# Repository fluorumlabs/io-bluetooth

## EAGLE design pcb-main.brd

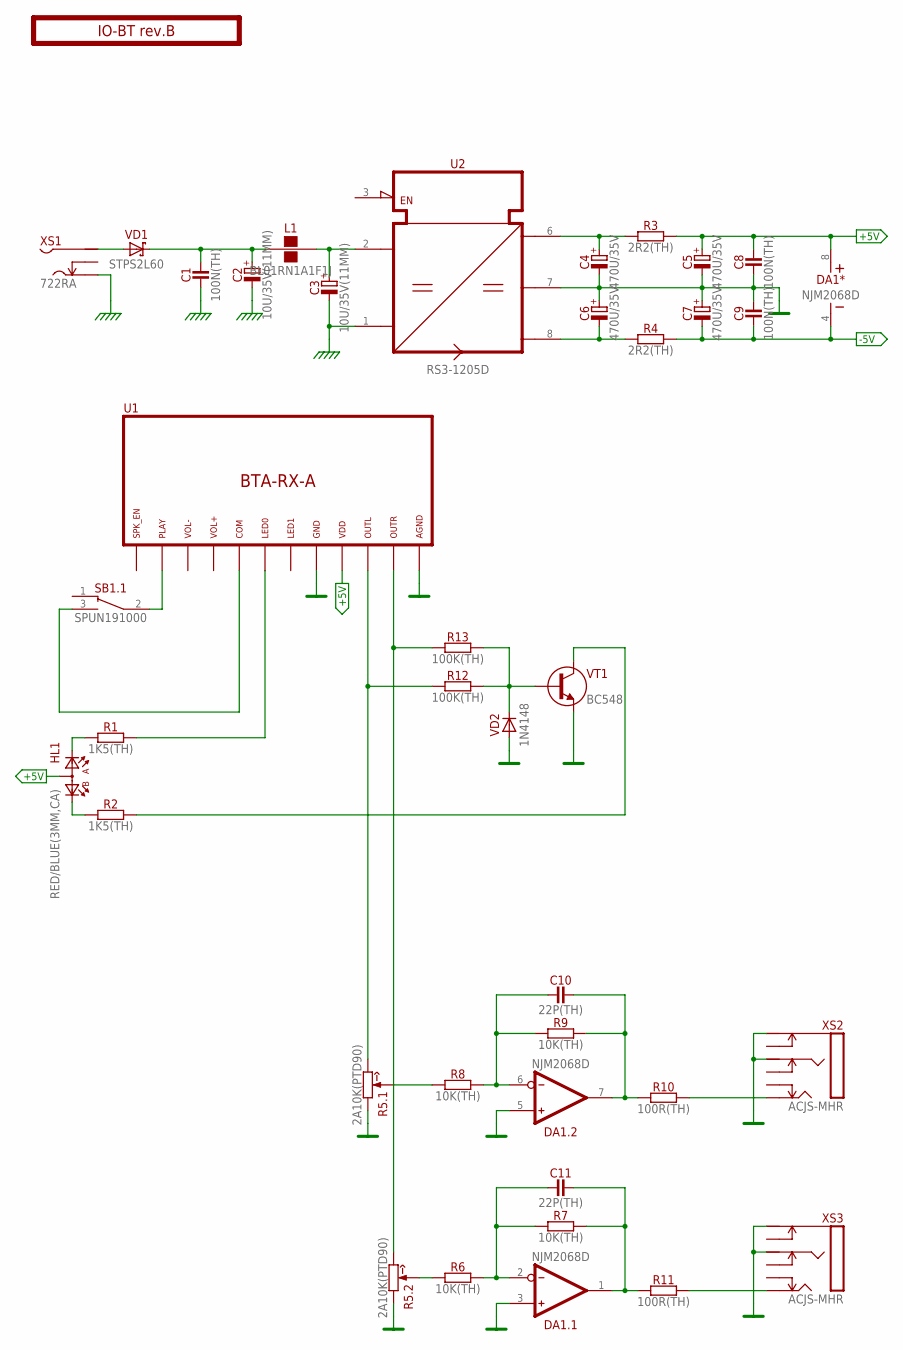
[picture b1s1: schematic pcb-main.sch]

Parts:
C1, C8, C9: 100N(TH); C050-024X044
C2, C3: 10U/35V(11MM); E2-5
C4, C5, C6, C7: 470U/35V; E5-10,5
C10, C11: 22P(TH); C050-024X044
DA1: NJM2068D; DIP-8
HL1: RED/BLUE(3MM,CA); DUOLED3MM-H
L1: BL01RN1A1F1J; BL01RN1A
PCB1: IO-BT rev.B; F-LOGO
R1, R2: 1K5(TH); R-0207/10
R3, R4: 2R2(TH); R-0207/10
R5: 2A10K(PTD90); PTD902
R6, R7, R8, R9: 10K(TH); R-0207/10
R10, R11: 100R(TH); R-0207/10
R12, R13: 100K(TH); R-0207/10
SB1: SPUN191000; SPUN-DPDT
U1: BTA-RX-A; BTA-RX
U2: RS3-1205D; SIP8
VD1: STPS2L60; DO41-10
VD2: 1N4148; DO35-7
VT1: BC548; TO92
XS1: 722RA; SWITCHCRAFT-L712RA
XS2, XS3: ACJS-MHR; NMJ6HC-S

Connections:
+5V: C5.+, C8.2, DA1.8 (V+), HL1.K (A), R3.2, U1.9
-5V: C7.-, C9.1, DA1.4 (V-), R4.2
CHASSIS: C1.1, C2.-, C3.-, U2.1 (IN-), XS1.S
GND: C4.-, C5.-, C6.+, C7.+, C8.1, C9.2, DA1.3 (IN+), DA1.5 (IN+), R5.A1 (CCW), R5.B1 (CCW), U1.8, U1.12, U2.7 (GND), VD2.A, VT1.3 (E), XS2.R, XS2.S, XS3.R, XS3.S
unnamed: C6.-, R4.1, U2.8 (V-)
unnamed: R5.A2 (W), R8.1
unnamed: R5.B2 (W), R6.1
unnamed: C11.1, DA1.2 (IN-), R6.2, R7.1
unnamed: C10.1, DA1.6 (IN-), R8.2, R9.1
unnamed: R5.A3 (CW), R12.1, U1.10
unnamed: R5.B3 (CW), R13.1, U1.11
unnamed: C10.2, DA1.7 (OUT), R9.2, R10.1
unnamed: C11.2, DA1.1 (OUT), R7.2, R11.1
unnamed: R10.2, XS2.T
unnamed: R11.2, XS3.T
unnamed: R2.2, VT1.1 (C)
unnamed: R12.2, R13.2, VD2.C, VT1.2 (B)
unnamed: SB1.2 (CM), U1.2
unnamed: SB1.3 (NO), U1.5
unnamed: HL1.A1 (K1), R1.1
unnamed: HL1.A2 (K2), R2.1
unnamed: R1.2, U1.6
unnamed: VD1.A, XS1.P
unnamed: C3.+, L1.2, U2.2 (IN+)
unnamed: C1.2, C2.+, L1.1, VD1.C
unnamed: C4.+, R3.1, U2.6 (V+)

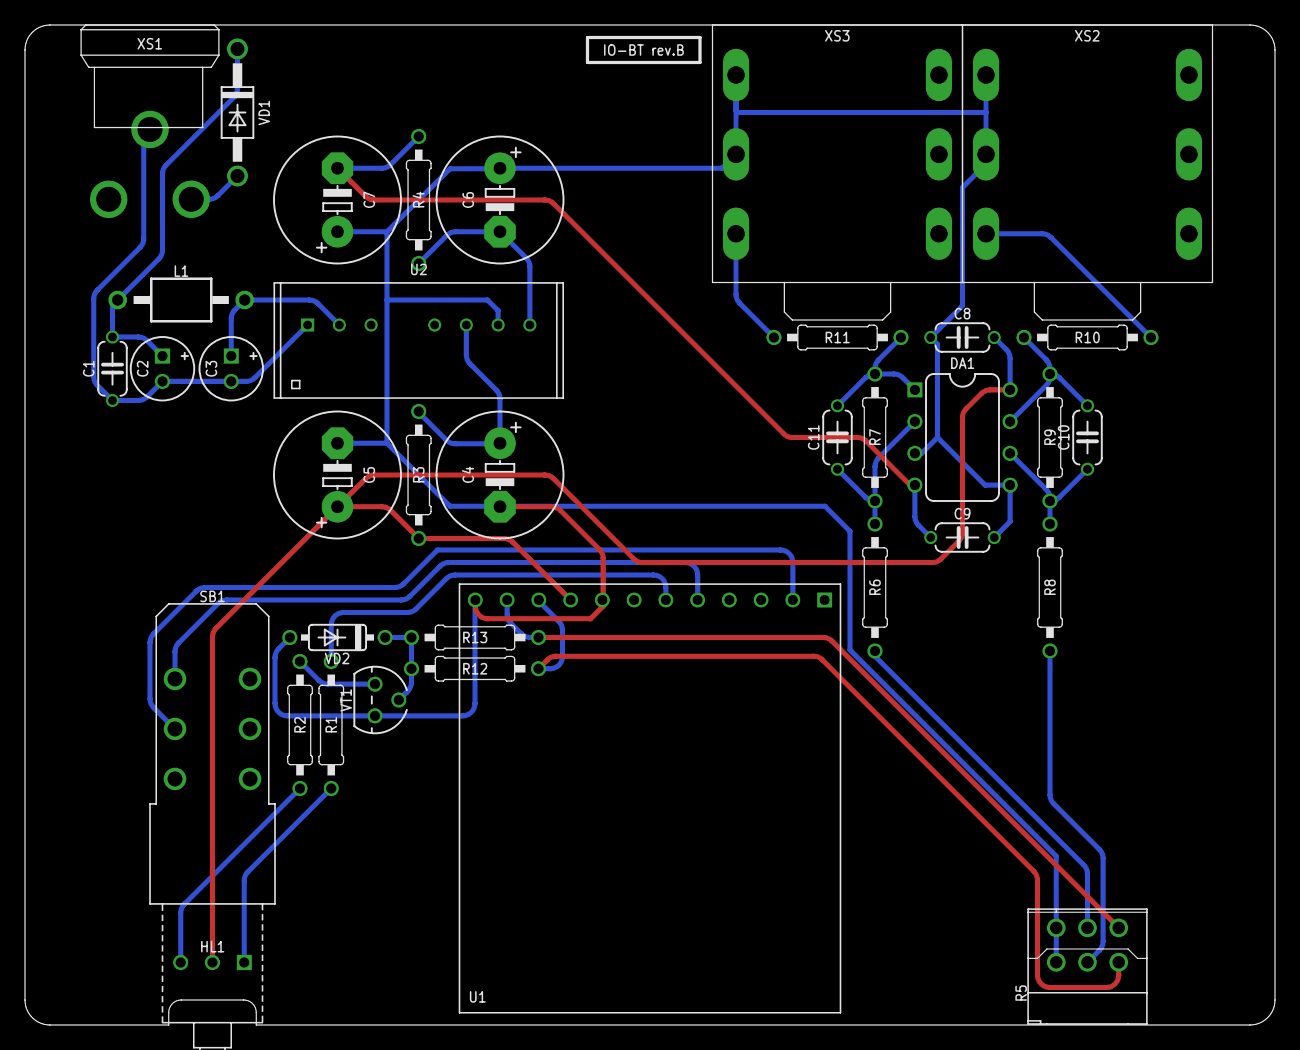
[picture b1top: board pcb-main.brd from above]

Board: 2 copper layers, 100.0 x 80.0 mm, 38 parts (0 on the bottom side), 26 nets.

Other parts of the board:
E$1: B*-080

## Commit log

2017-03-01 Schematic and PCB ready
2017-03-01 Fix LED Position
2017-03-01 Component rename
2017-03-02 Change DC Connector
2017-03-06 Fix Boardoutline
2017-03-10 Front and back panels
2017-03-10 Swap Prev/Next Buttons
2017-03-10 Bump board revision
2017-03-10 Front panel update
2017-03-20 Increase TRS connector spacing (#1)
2017-03-20 Change TRS positioning (#1)
2017-03-20 Change LED mounting cutout (#2)
2017-03-20 Fix ALPS SPUN footprint drills (#4)
2017-06-03 Updates
    - Added output volume potentiometer
    - Blue LED is now used for signal indicator
    - Removed next/prev buttons
2017-06-09 Change switch position
2020-12-02 Add .whitesource configuration file
